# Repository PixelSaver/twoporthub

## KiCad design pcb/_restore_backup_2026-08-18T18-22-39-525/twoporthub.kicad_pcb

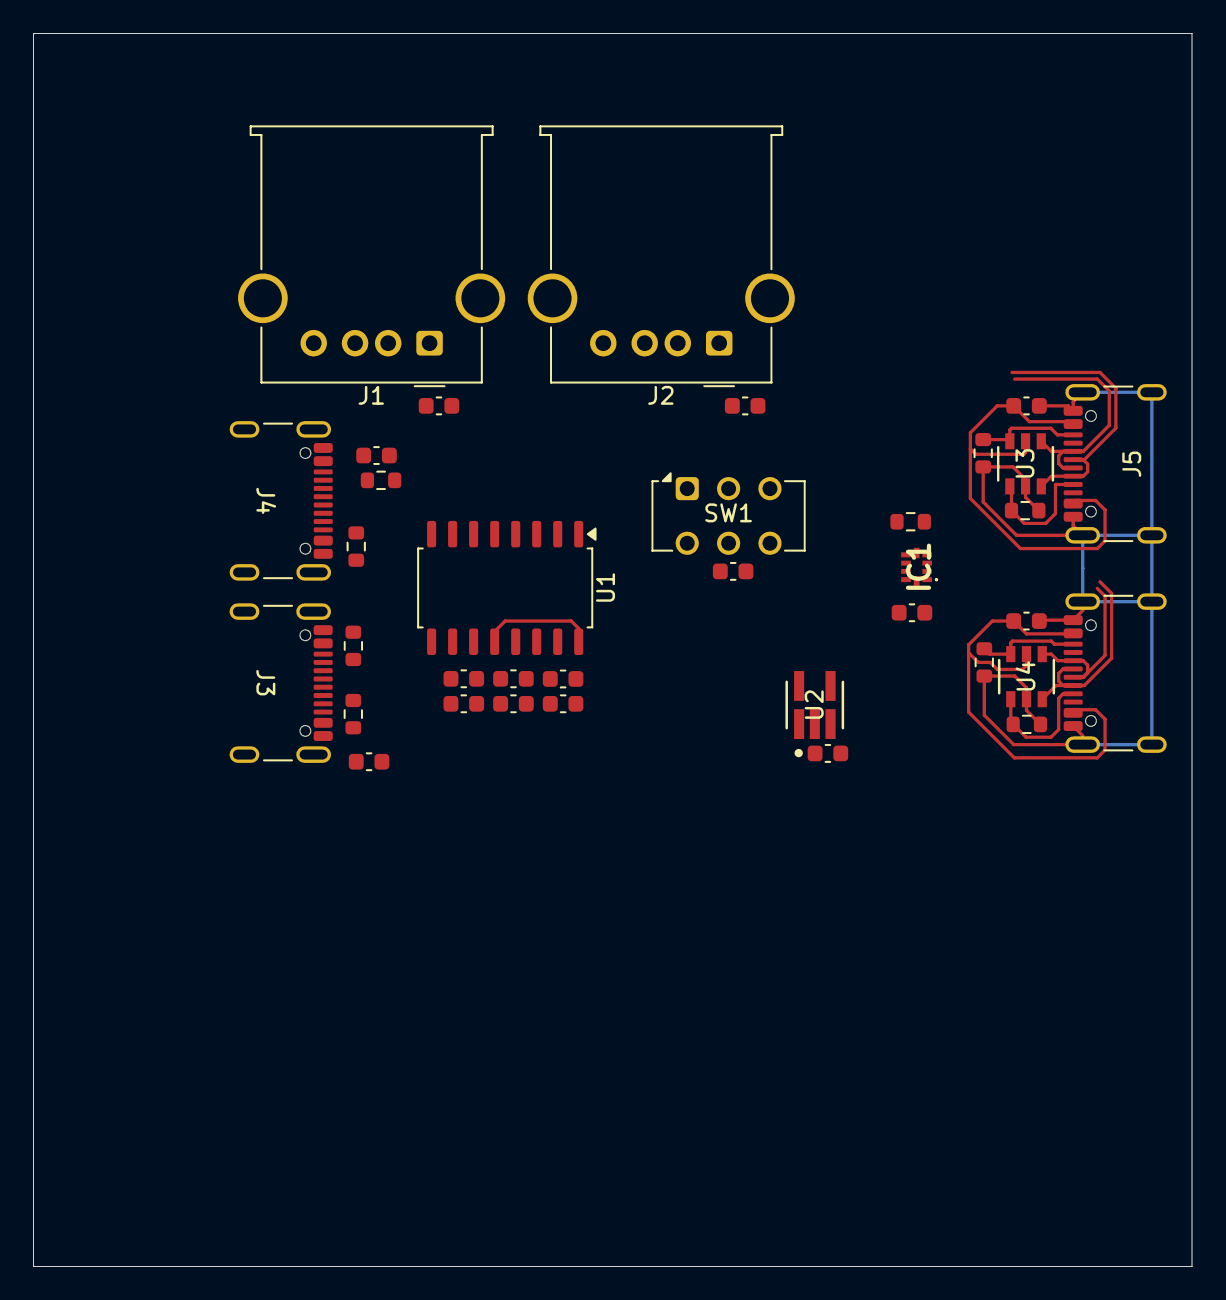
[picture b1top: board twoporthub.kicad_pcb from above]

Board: 2 copper layers, 70.0 x 74.5 mm, 36 parts (0 on the bottom side), 30 nets.

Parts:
C1, C3, C4, C5, C6, C7, C9, C11, C12, C13: 1uF; C_0603_1608Metric
C2, C8, C10, C14, C15: 100nF; C_0603_1608Metric
IC1: TS3USB221ERSER
J1, J2: USB_A; USB_A_Molex_67643_Horizontal
J3, J4, J5, J6: USB_C_16P; USB_C_Receptacle_GCT_USB4105-xx-A_16P_TopMnt_Horizontal
R1, R2, R3, R4: 56kΩ; R_0603_1608Metric
R5: 10kΩ; R_0603_1608Metric
R6, R7, R8, R9: 5.1kΩ; R_0603_1608Metric
SW1: SW_Push_DPDT; SW_CK_JS202011CQN_DPDT_Straight
U1: SL2.1A; SOIC-16_4.55x10.3mm_P1.27mm
U2: TLV77312PDBVR; DBV0005A-IPC_A
U3, U4: TPD4E001DBVR; DBV6

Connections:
+3.3V: C12.2, C13.1, IC1.10 (VCC), SW1.5 (B), U2.5 (OUT)
+5V: C3.1, C4.1, C5.1, C6.1, C9.1, C10.1, C11.2, J1.1 (VBUS), J2.1 (VBUS), J3.A4 (VBUS), J3.A9 (VBUS), J3.B4 (VBUS), J3.B9 (VBUS), J4.A4 (VBUS), J4.A9 (VBUS), J4.B4 (VBUS), J4.B9 (VBUS), R1.1, R2.1, R3.1, R4.1, SW1.2 (B), U1.11 (VCC5V), U2.1 (IN), U2.3 (EN)
BYPASS: C1.2, C2.2, C3.2, C4.2, C5.2, C6.2, C7.2, C8.2, C9.2, C10.2, C11.1, C12.1, C13.2, C14.2, C15.2, IC1.5 (GND), IC1.6 (~OE), J1.4 (GND), J1.SH (Shield), J2.4 (GND), J2.SH (Shield), J3.A1 (GND), J3.A12 (GND), J3.B1 (GND), J3.B12 (GND), J3.SH (SHIELD), J4.A1 (GND), J4.A12 (GND), J4.B1 (GND), J4.B12 (GND), J4.SH (SHIELD), J5.A1 (GND), J5.A12 (GND), J5.B1 (GND), J5.B12 (GND), J5.SH (SHIELD), J6.A1 (GND), J6.A12 (GND), J6.B1 (GND), J6.B12 (GND), J6.SH (SHIELD), R5.2, R6.1, R7.1, R8.1, R9.1, SW1.4 (A), U1.12 (GND), U1.16 (XIN), U2.2 (GND), U2.4 (NC), U3.2 (GND), U4.2 (GND)
D1+: J3.A6 (D+), J3.B6 (D+), U1.8 (DP1)
D1-: J3.A7 (D-), J3.B7 (D-), U1.7 (DM1)
D2+: J4.A6 (D+), J4.B6 (D+), U1.6 (DP2)
D2-: J4.A7 (D-), J4.B7 (D-), U1.5 (DM2)
D3+: J1.3 (D+), U1.4 (DP3)
D3-: J1.2 (D-), U1.3 (DM3)
D4+: J2.3 (D+), U1.2 (DP4)
D4-: J2.2 (D-), U1.1 (DM4)
D+: IC1.8 (D+), U1.10 (UDP)
D-: IC1.7 (D-), U1.9 (UDM)
IN1_CC1: J5.A5 (CC1), R8.2, U3.1 (IO1)
IN1_CC2: J5.B5 (CC2), R6.2, U3.6 (IO4)
IN1_D+: IC1.1 (1D+), J5.A6 (D+), J5.B6 (D+), U3.4 (IO3)
IN1_D-: IC1.2 (1D-), J5.A7 (D-), J5.B7 (D-), U3.3 (IO2)
IN2_CC1: J6.A5 (CC1), R9.2, U4.1 (IO1)
IN2_CC2: J6.B5 (CC2), R7.2, U4.6 (IO4)
IN2_D+: IC1.3 (2D+), J6.A6 (D+), J6.B6 (D+), U4.4 (IO3)
IN2_D-: IC1.4 (2D-), J6.A7 (D-), J6.B7 (D-), U4.3 (IO2)
unnamed: IC1.9 (S), R5.1, SW1.6 (C)
unnamed: J3.A5 (CC1), R1.2
unnamed: J3.B5 (CC2), R2.2
unnamed: J4.A5 (CC1), R3.2
unnamed: J4.B5 (CC2), R4.2
unnamed: C7.1, C8.1, U1.13 (VDD3)
unnamed: C1.1, C2.1, U1.14 (VDD18)
VBUS1: C14.1, J5.A4 (VBUS), J5.A9 (VBUS), J5.B4 (VBUS), J5.B9 (VBUS), SW1.3 (C), U3.5 (VCC)
VBUS2: C15.1, J6.A4 (VBUS), J6.A9 (VBUS), J6.B4 (VBUS), J6.B9 (VBUS), SW1.1 (A), U4.5 (VCC)
